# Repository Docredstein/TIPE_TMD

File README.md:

# TIPE_TMD
TIPE TMD 2022-2023
Ici se trouve le repo de notre TIPE ayant pour thème la ville, si vous êtes aussi en prépa libre à vous de vous inspirer, En cas de besoin vous pouvez envoyer un mail à
mateis. frambourt @laposte.net (sans les espaces) et je ferais de mon mieux pour vous aider.

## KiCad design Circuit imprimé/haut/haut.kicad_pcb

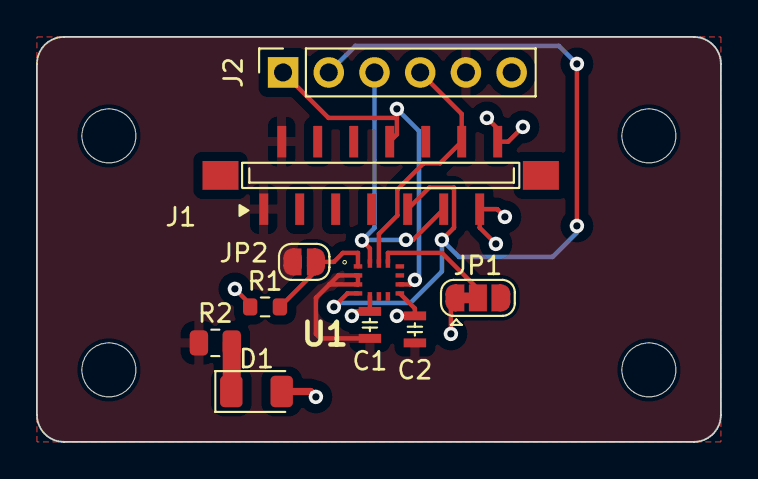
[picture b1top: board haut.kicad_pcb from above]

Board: 2 copper layers, 38.0 x 22.5 mm, 10 parts (0 on the bottom side), 9 nets.

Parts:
C1, C2: 100n; Cap 100nf 0805
D1: LED; LED_1206_3216Metric
J1: Conn_01x14_Shielded; FPC 2x7 p=1mm
J2: Conn_01x06_Male; PinSocket_1x06_P2.54mm_Vertical
JP1: SolderJumper_3_Bridged12; SolderJumper-3_P1.3mm_Bridged12_RoundedPad1.0x1.5mm
JP2: SolderJumper_2_Open; SolderJumper-2_P1.3mm_Open_RoundedPad1.0x1.5mm
R1: 10k; R_0603_1608Metric
R2: 30; R_0805_2012Metric
U1: LSM6DSRTR; LGA-14_2.5X3X0.86_

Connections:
+3V3: C1.1, C2.1, D1.2 (A), J1.13, J1.14, J2.6, JP1.1 (A), R1.1, U1.5 (VDD_IO), U1.8 (VDD)
GND: C1.2, C2.2, J1.1, J1.2, J2.5, JP2.2 (B), R2.1, U1.2 (SDX_), U1.3 (SCX)
INT1_Haut: J1.9, J2.2, U1.4 (INT1)
INT2_Haut: J1.8, J2.1, U1.9 (INT2)
unnamed: D1.1 (K), R2.2
unnamed: JP1.2 (C), U1.12 (CS)
unnamed: JP2.1 (A), R1.2, U1.1 (SDO/SA0)
SCL: J1.12, J2.4, U1.13 (SCL)
SDA: J1.11, J2.3, U1.14 (SDA)

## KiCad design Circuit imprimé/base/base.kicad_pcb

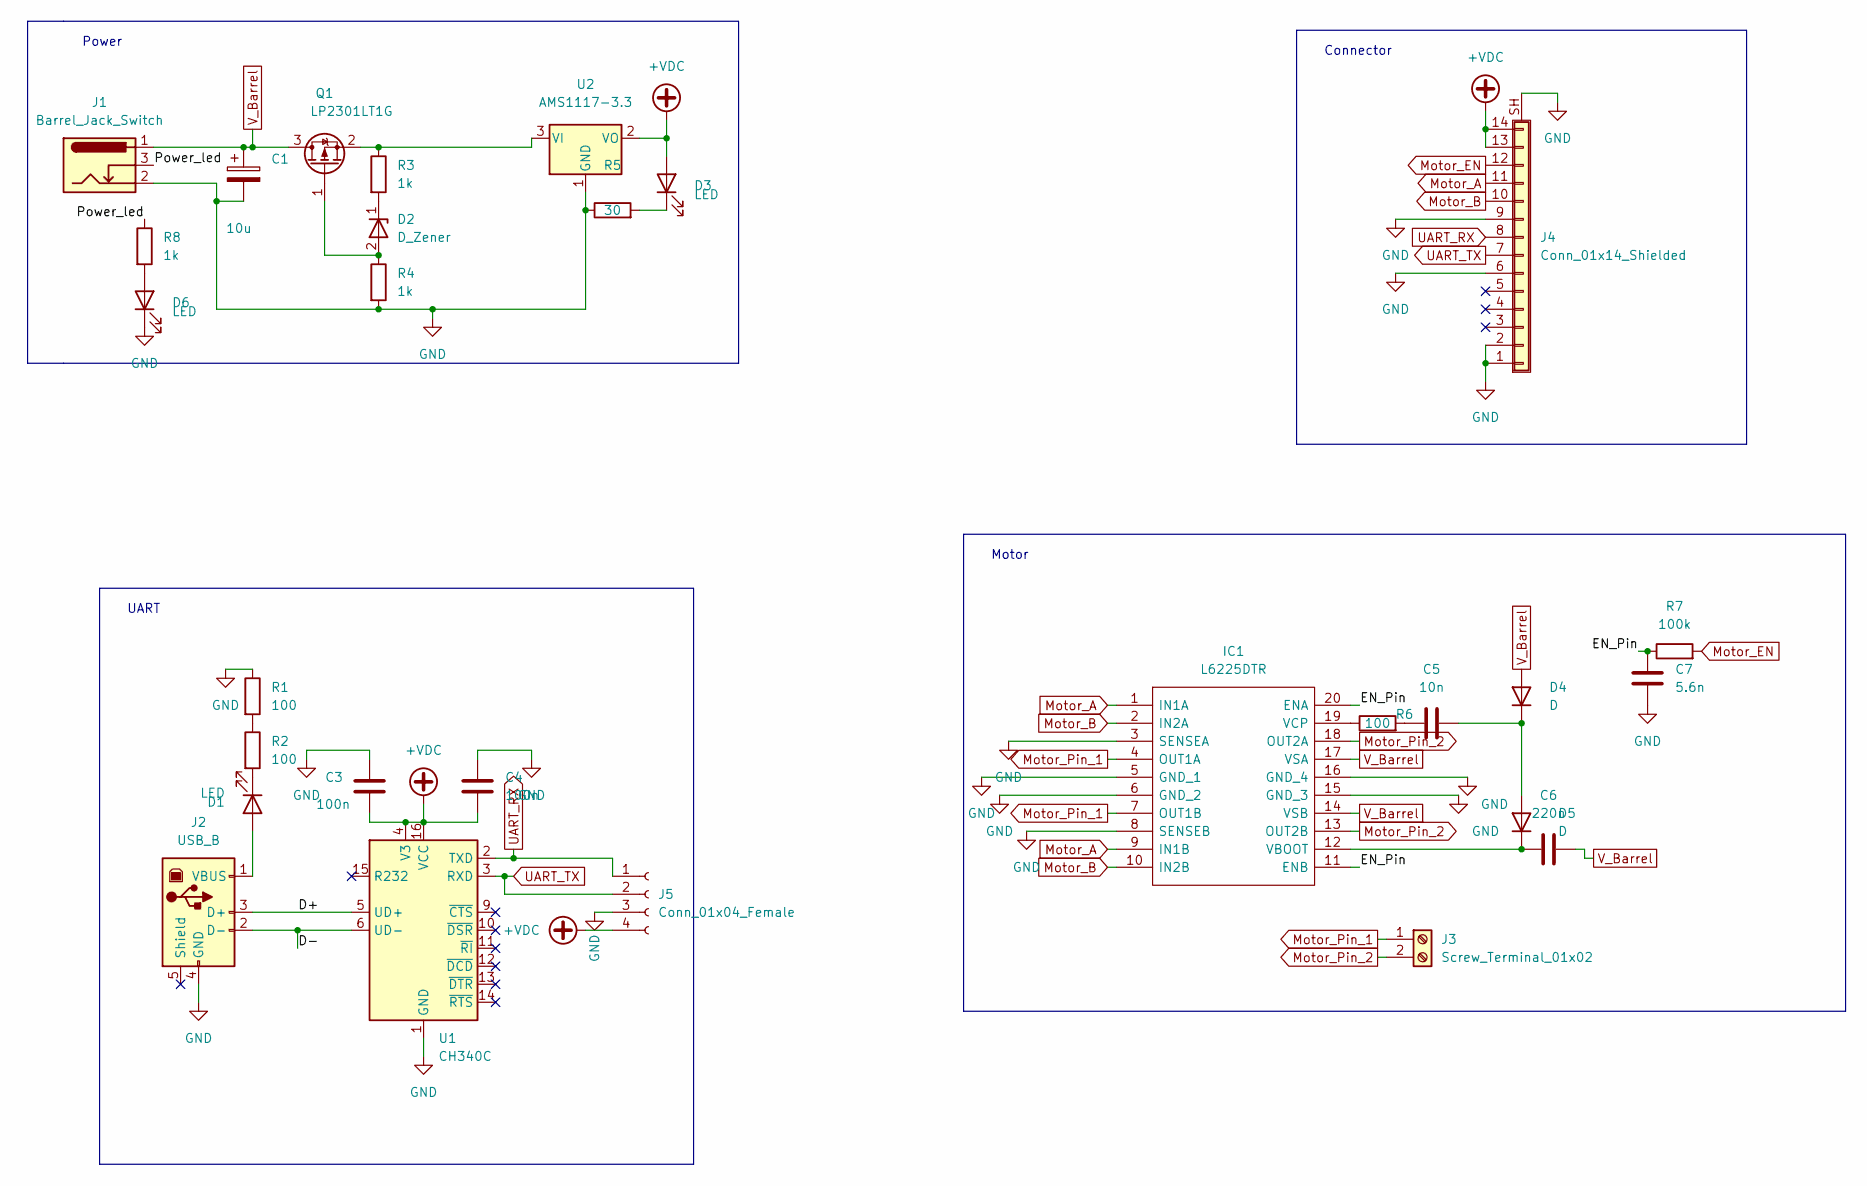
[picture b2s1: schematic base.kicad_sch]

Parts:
C1: 10u; CP_Elec_6.3x7.7
C3, C4: 100n; Cap 100nf 0805
C5: 10n; C_0805_2012Metric
C6: 220n; C_0805_2012Metric
C7: 5.6n; C_0603_1608Metric
D1, D3, D6: LED; LED_1206_3216Metric
D2: D_Zener; SOD223
D4, D5: D; D_SOD-323
IC1: L6225DTR; Mouser Part Number 511-L6225DTR
J1: Barrel_Jack_Switch; BarrelJack_GCT_DCJ200-10-A_Horizontal
J2: USB_B; USB_B_OST_USB-B1HSxx_Horizontal
J3: Screw_Terminal_01x02; TerminalBlock_Dinkle_DT-55-B01X-02_P10.00mm
J4: Conn_01x14_Shielded; FPC 2x7 p=1mm
J5: Conn_01x04_Female; PinSocket_1x04_P2.54mm_Horizontal
Q1: LP2301LT1G; SOT-23
R1, R2, R6: 100; R_0603_1608Metric
R3, R4, R8: 1k; R_0603_1608Metric
R5: 30; R_0805_2012Metric
R7: 100k; R_0603_1608Metric
U1: CH340C; SOIC-16_3.9x9.9mm_P1.27mm
U2: AMS1117-3.3; SOT-223-3_TabPin2

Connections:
+VDC: C3.2, C4.1, D3.2 (A), J4.13, J4.14, J5.4, U1.4 (V3), U1.16 (VCC), U2.2 (VO)
/D+: J2.3 (D+), U1.5 (UD+)
/D-: J2.2 (D-), U1.6 (UD-)
/EN_Pin: C7.2, IC1.11 (ENB), IC1.20 (ENA), R7.1
/Power_led: J1.3, R8.1
GND: C1.2, C3.1, C4.2, C7.1, D6.1 (K), IC1.3 (SENSEA), IC1.5 (GND_1), IC1.6 (GND_2), IC1.8 (SENSEB), IC1.15 (GND_3), IC1.16 (GND_4), J1.2, J2.4 (GND), J4.1, J4.2, J4.6, J4.9, J4.SH (Shield), J5.3, R1.1, R4.2, R5.1, U1.1 (GND), U2.1 (GND)
Motor_A: IC1.1 (IN1A), IC1.9 (IN1B), J4.11
Motor_B: IC1.2 (IN2A), IC1.10 (IN2B), J4.10
Motor_EN: J4.12, R7.2
Motor_Pin_1: IC1.4 (OUT1A), IC1.7 (OUT1B), J3.1
Motor_Pin_2: IC1.13 (OUT2B), IC1.18 (OUT2A), J3.2
unnamed: C5.1, R6.2
unnamed: C5.2, D4.1 (K), D5.2 (A)
unnamed: C6.1, D5.1 (K), IC1.12 (VBOOT)
unnamed: D1.1 (K), R2.2
unnamed: D1.2 (A), J2.1 (VBUS)
unnamed: D2.1 (K), R3.2
unnamed: D2.2 (A), Q1.1 (G), R4.1
unnamed: D3.1 (K), R5.2
unnamed: D6.2 (A), R8.2
unnamed: IC1.19 (VCP), R6.1
unnamed: Q1.2 (S), R3.1, U2.3 (VI)
unnamed: R1.2, R2.1
UART_RX: J4.8, J5.1, U1.2 (TXD)
UART_TX: J4.7, J5.2, U1.3 (RXD)
V_Barrel: C1.1, C6.2, D4.2 (A), IC1.14 (VSB), IC1.17 (VSA), J1.1, Q1.3 (D)

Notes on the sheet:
Power
Motor
UART
Connector

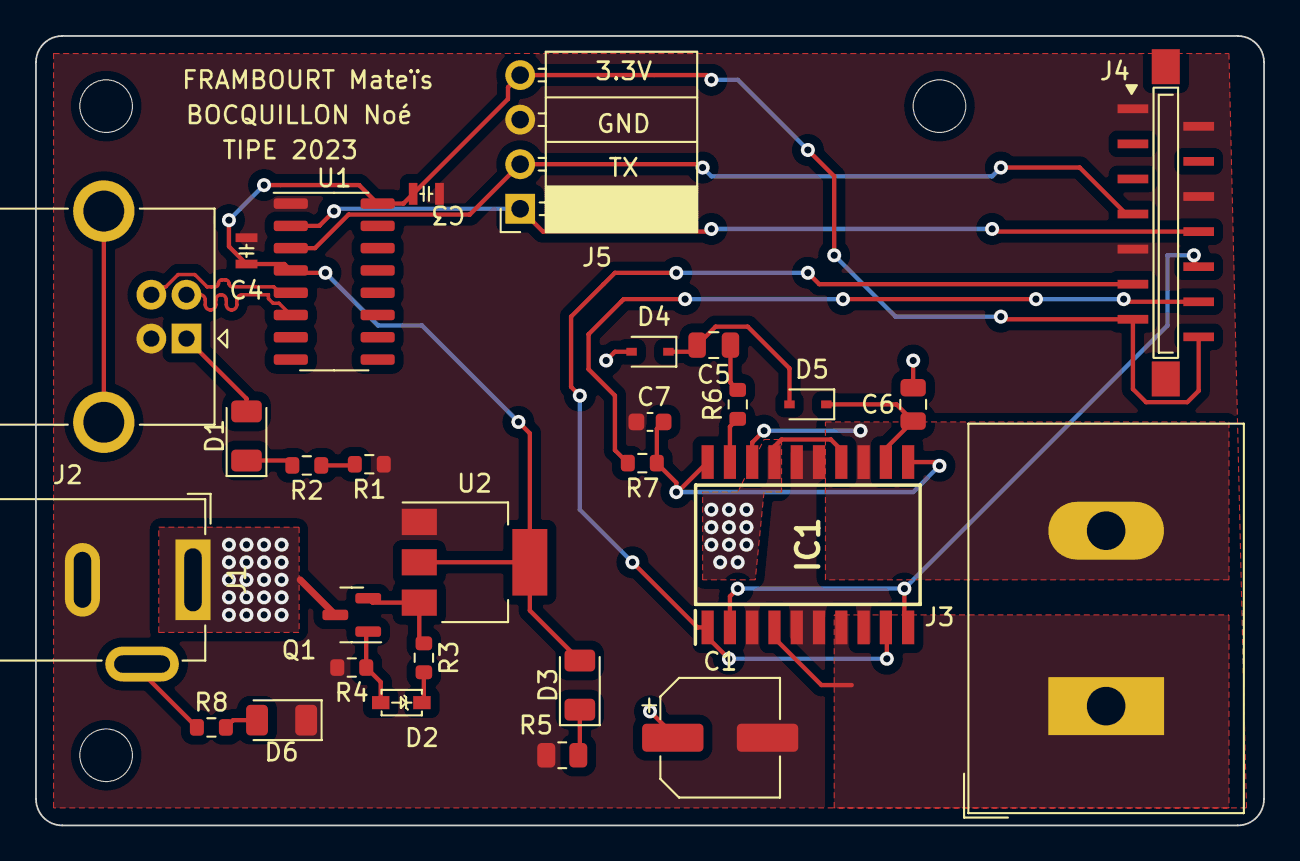
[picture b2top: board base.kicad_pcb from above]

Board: 2 copper layers, 70.0 x 45.0 mm, 29 parts (0 on the bottom side), 26 nets.

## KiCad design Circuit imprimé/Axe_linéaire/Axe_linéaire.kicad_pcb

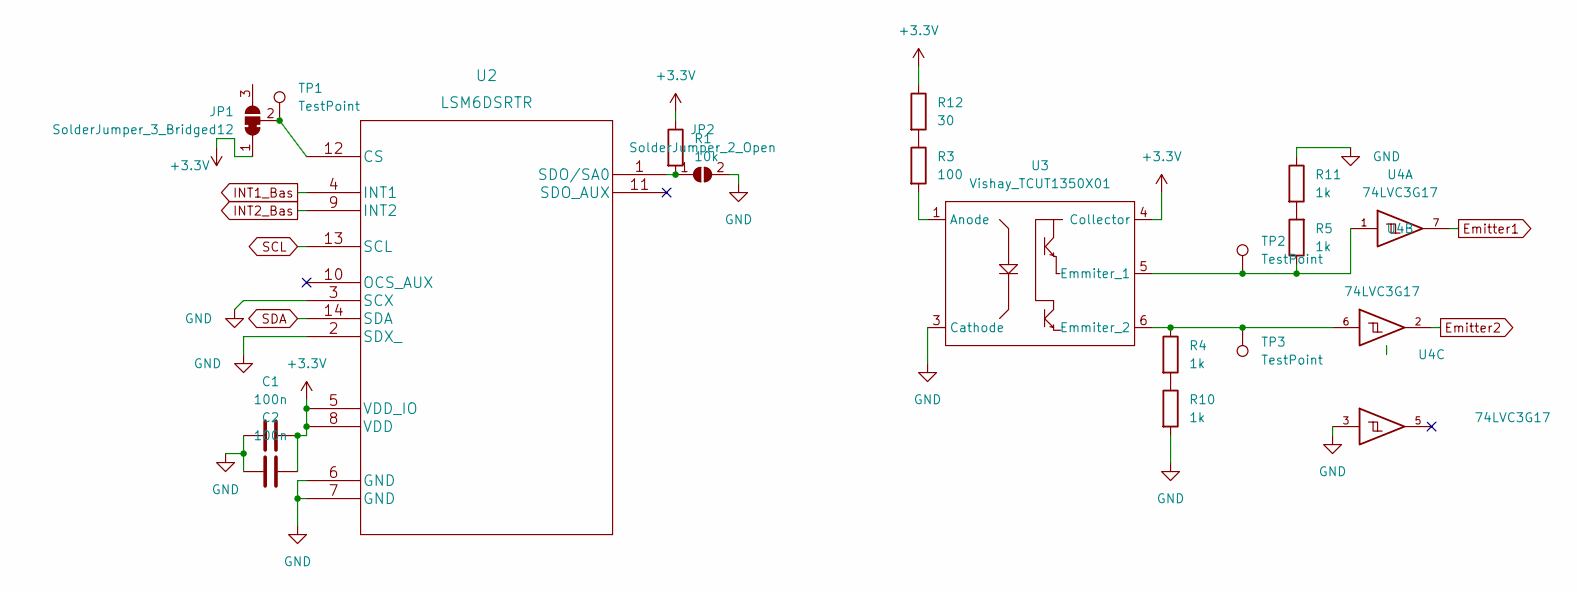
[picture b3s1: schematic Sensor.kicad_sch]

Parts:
C1, C2: 100n; Cap 100nf 0805
JP1: SolderJumper_3_Bridged12; SolderJumper-3_P1.3mm_Bridged12_RoundedPad1.0x1.5mm
JP2: SolderJumper_2_Open; SolderJumper-2_P1.3mm_Open_RoundedPad1.0x1.5mm
R1: 10k; R_0603_1608Metric
R3: 100; R_0603_1608Metric
R4, R5, R10, R11: 1k; R_0603_1608Metric
R12: 30; R_0805_2012Metric
TP1, TP2, TP3: TestPoint; TestPoint_Pad_D2.0mm
U2: LSM6DSRTR; LGA-14_2.5X3X0.86_
U3: Vishay_TCUT1350X01; Vishay TCUT1350X01
U4: 74LVC3G17; VSSOP-8_2.3x2mm_P0.5mm

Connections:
+3.3V: C1.1, C2.1, JP1.1 (A), R1.1, R12.1, U2.5 (VDD_IO), U2.8 (VDD), U3.4 (Collector), U4.8 (+3.3V); also elsewhere on the board
Emitter1: U4.7; also elsewhere on the board
Emitter2: U4.2; also elsewhere on the board
GND: C1.2, C2.2, JP2.2 (B), R10.2, R11.1, U2.2 (SDX_), U2.3 (SCX), U2.6 (GND), U2.7 (GND), U3.3 (Cathode), U4.3, U4.4 (GND); also elsewhere on the board
INT1_Bas: U2.4 (INT1); also elsewhere on the board
INT2_Bas: U2.9 (INT2); also elsewhere on the board
unnamed: JP1.2 (C), TP1.1, U2.12 (CS)
unnamed: JP2.1 (A), R1.2, U2.1 (SDO/SA0)
unnamed: R3.2, U3.1 (Anode)
unnamed: R4.1, TP3.1, U3.6 (Emmiter_2), U4.6
unnamed: R5.1, TP2.1, U3.5 (Emmiter_1), U4.1
unnamed: R4.2, R10.1
unnamed: R5.2, R11.2
unnamed: R3.1, R12.2
SCL: U2.13 (SCL); also elsewhere on the board
SDA: U2.14 (SDA); also elsewhere on the board

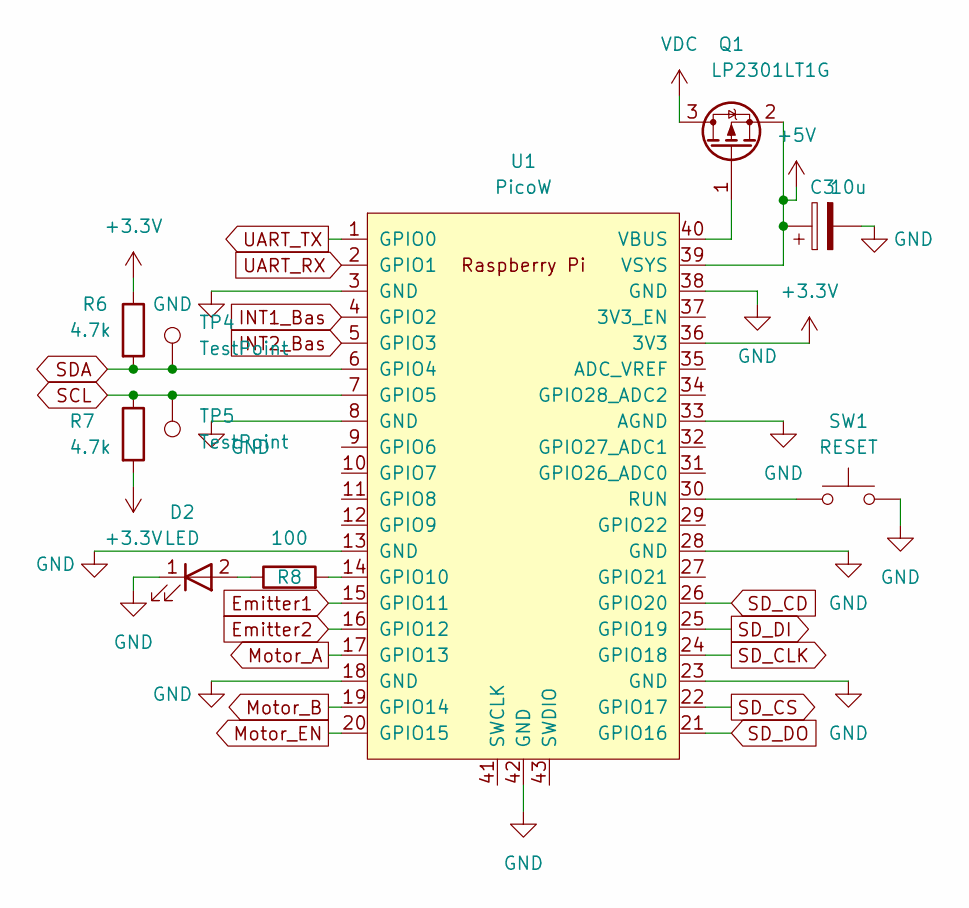
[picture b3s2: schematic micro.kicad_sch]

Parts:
C3: 10u; CP_Elec_6.3x7.7
D2: LED; UV_LED
Q1: LP2301LT1G; SOT-23
R6, R7: 4.7k; R_0603_1608Metric
R8: 100; R_0603_1608Metric
SW1: RESET; Tactile Button
TP4, TP5: TestPoint; TestPoint_Pad_D2.0mm
U1: PicoW; RPi_PicoW_SMD_TH

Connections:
+3.3V: R6.1, R7.2, U1.36 (3V3); also elsewhere on the board
+5V: C3.1, Q1.2 (S), U1.39 (VSYS)
Emitter1: U1.15 (GPIO11); also elsewhere on the board
Emitter2: U1.16 (GPIO12); also elsewhere on the board
GND: C3.2, D2.1 (K), SW1.3 (B), SW1.4 (B), U1.3 (GND), U1.8 (GND), U1.13 (GND), U1.18 (GND), U1.23 (GND), U1.28 (GND), U1.33 (AGND), U1.38 (GND), U1.42 (GND); also elsewhere on the board
INT1_Bas: U1.4 (GPIO2); also elsewhere on the board
INT1_Haut: U1.9 (GPIO6); also elsewhere on the board
INT2_Bas: U1.5 (GPIO3); also elsewhere on the board
INT2_Haut: U1.10 (GPIO7); also elsewhere on the board
Motor_A: U1.17 (GPIO13); also elsewhere on the board
Motor_B: U1.19 (GPIO14); also elsewhere on the board
Motor_EN: U1.20 (GPIO15); also elsewhere on the board
unnamed: D2.2 (A), R8.1
unnamed: Q1.1 (G), U1.40 (VBUS)
unnamed: R8.2, U1.14 (GPIO10)
unnamed: SW1.1 (A), SW1.2 (A), U1.30 (RUN)
SCL: R7.1, TP5.1, U1.7 (GPIO5); also elsewhere on the board
SDA: R6.2, TP4.1, U1.6 (GPIO4); also elsewhere on the board
SD_CD: U1.26 (GPIO20); also elsewhere on the board
SD_CLK: U1.24 (GPIO18); also elsewhere on the board
SD_CS: U1.22 (GPIO17); also elsewhere on the board
SD_DI: U1.25 (GPIO19); also elsewhere on the board
SD_DO: U1.21 (GPIO16); also elsewhere on the board
UART_RX: U1.2 (GPIO1); also elsewhere on the board
UART_TX: U1.1 (GPIO0); also elsewhere on the board
VDC: Q1.3 (D); also elsewhere on the board

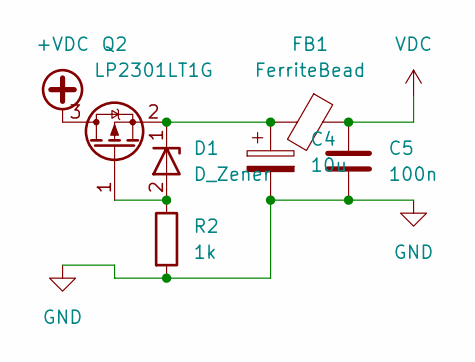
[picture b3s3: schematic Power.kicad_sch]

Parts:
C4: 10u; CP_Elec_6.3x7.7
C5: 100n; Cap 100nf 0805
D1: D_Zener; SOD223
FB1: FerriteBead; ferrite Bead
Q2: LP2301LT1G; SOT-23
R2: 1k; R_0603_1608Metric

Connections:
+VDC: Q2.3 (D); also elsewhere on the board
GND: C4.2, C5.2, R2.2; also elsewhere on the board
unnamed: C4.1, D1.1 (K), FB1.2, Q2.2 (S)
unnamed: D1.2 (A), Q2.1 (G), R2.1
VDC: C5.1, FB1.1; also elsewhere on the board

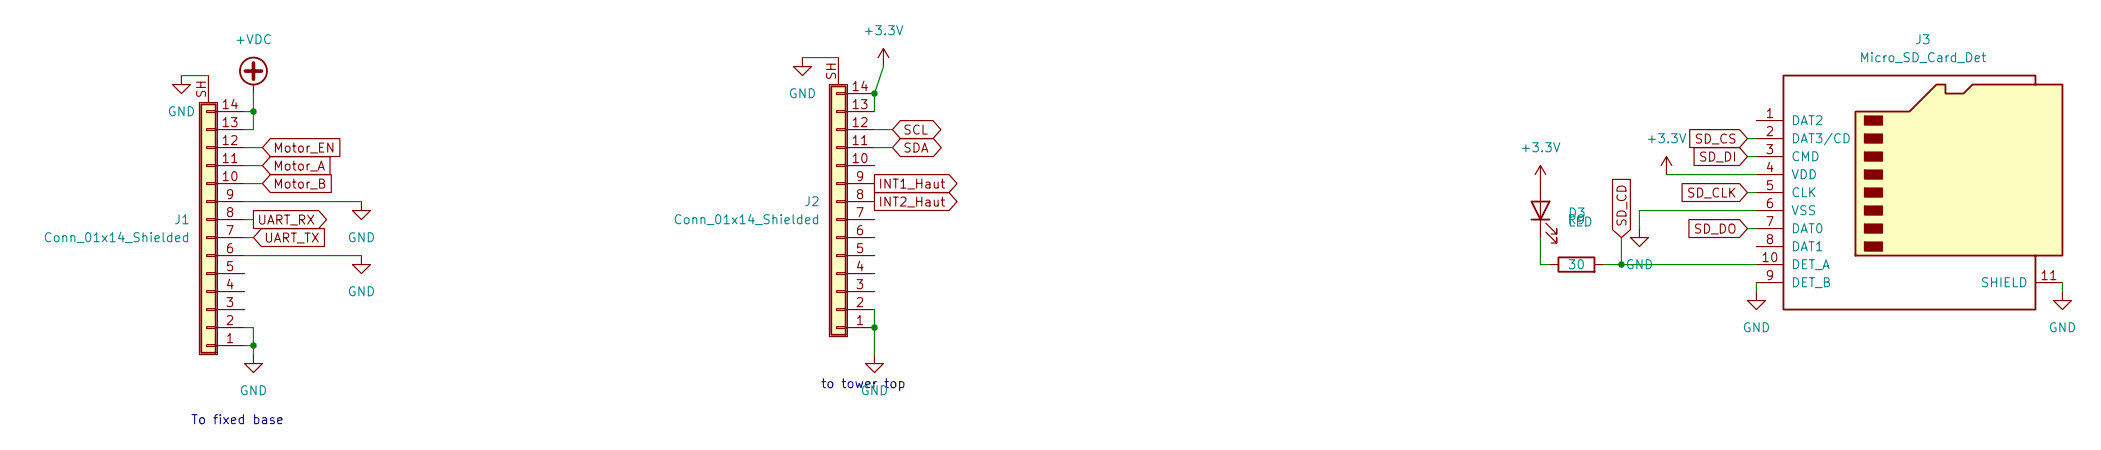
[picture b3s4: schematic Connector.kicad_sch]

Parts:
D3: LED; LED_1206_3216Metric
J1, J2: Conn_01x14_Shielded; FPC 2x7 p=1mm
J3: Micro_SD_Card_Det; microSD_HC_Hirose_DM3AT-SF-PEJM5
R9: 30; R_0805_2012Metric

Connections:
+3.3V: D3.2 (A), J2.13, J2.14, J3.4 (VDD); also elsewhere on the board
+VDC: J1.13, J1.14; also elsewhere on the board
GND: J1.1, J1.2, J1.6, J1.9, J1.SH (Shield), J2.1, J2.2, J2.SH (Shield), J3.6 (VSS), J3.9 (DET_B), J3.11 (SHIELD); also elsewhere on the board
INT1_Haut: J2.9; also elsewhere on the board
INT2_Haut: J2.8; also elsewhere on the board
Motor_A: J1.11; also elsewhere on the board
Motor_B: J1.10; also elsewhere on the board
Motor_EN: J1.12; also elsewhere on the board
unnamed: D3.1 (K), R9.1
SCL: J2.12; also elsewhere on the board
SDA: J2.11; also elsewhere on the board
SD_CD: J3.10 (DET_A), R9.2; also elsewhere on the board
SD_CLK: J3.5 (CLK); also elsewhere on the board
SD_CS: J3.2 (DAT3/CD); also elsewhere on the board
SD_DI: J3.3 (CMD); also elsewhere on the board
SD_DO: J3.7 (DAT0); also elsewhere on the board
UART_RX: J1.8; also elsewhere on the board
UART_TX: J1.7; also elsewhere on the board

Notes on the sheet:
To fixed base
to tower top

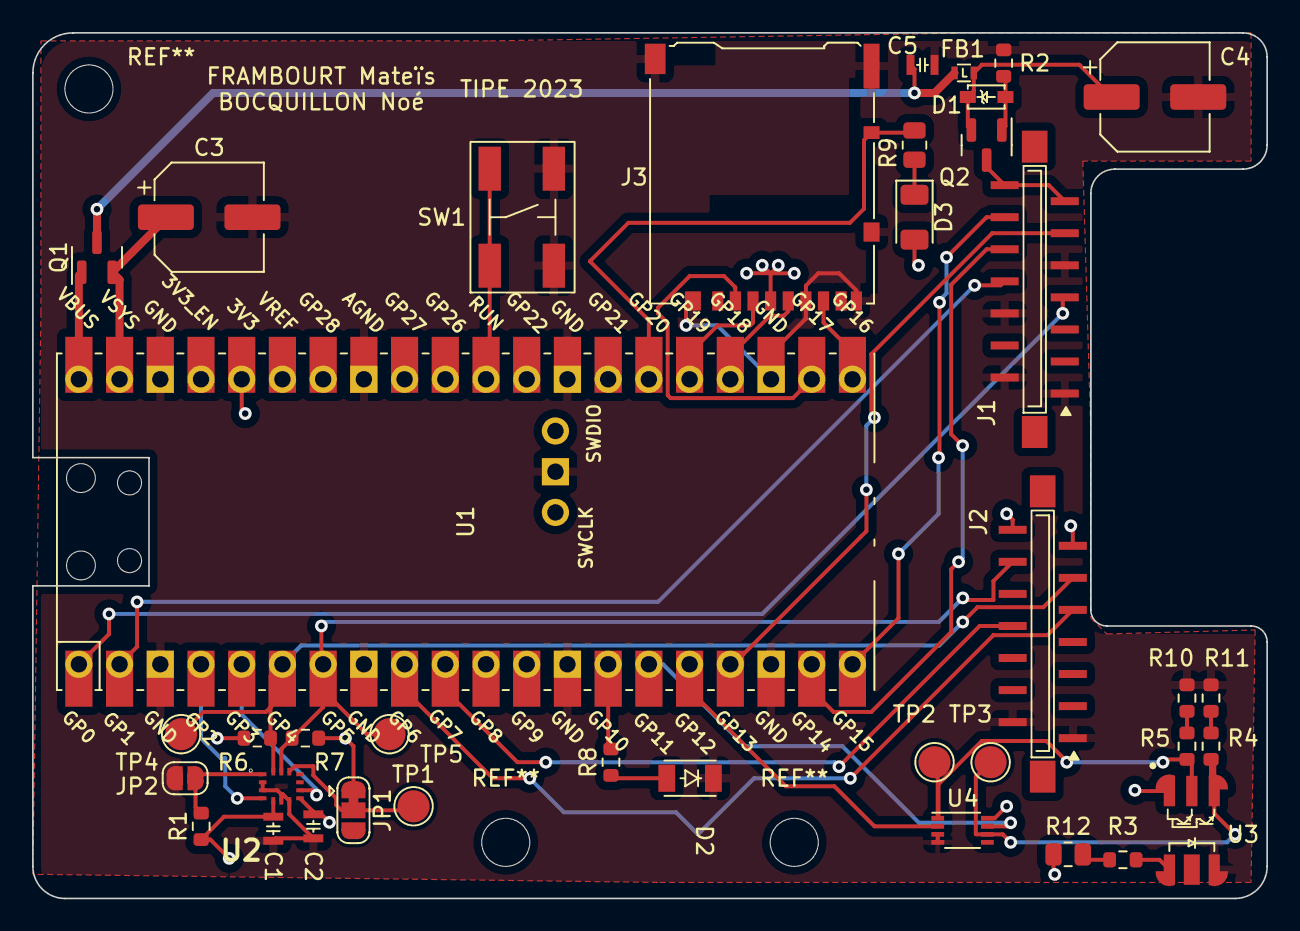
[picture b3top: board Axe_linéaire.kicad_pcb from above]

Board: 2 copper layers, 77.0 x 54.0 mm, 38 parts (0 on the bottom side), 38 nets.

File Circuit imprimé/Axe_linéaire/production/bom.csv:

Designator,Footprint,Quantity,Value,LCSC Part #
"C1, C2, C5",Cap 100nf 0805,3,100n,
"C3, C4",CP_Elec_6.3x7.7,2,10u,
D1,SOD223,1,D_Zener,
D2,UV_LED,1,LED,
D3,1206,1,LED,
FB1,ferrite Bead,1,FerriteBead,
"J1, J2",FPC 2x7 p=1mm,2,Conn_01x14_Shielded,
J3,microSD_HC_Hirose_DM3AT-SF-PEJM5,1,Micro_SD_Card_Det,
JP1,SolderJumper-3_P1.3mm_Bridged12_RoundedPad1.0x1.5mm,1,SolderJumper_3_Bridged12,
JP2,SolderJumper-2_P1.3mm_Open_RoundedPad1.0x1.5mm,1,SolderJumper_2_Open,
"Q1, Q2",SOT-23,2,LP2301LT1G,
R1,0603,1,10k,
R10,0603,1,1k,
R11,0603,1,1k,
R12,0805,1,30,
R2,0603,1,1k,
R3,0603,1,100,
R4,0603,1,1k,
R5,0603,1,1k,
R6,0603,1,4.7k,
R7,0603,1,4.7k,
R8,0603,1,100,
R9,0805,1,30,
SW1,Tactile Button,1,RESET,
"TP1, TP2, TP3, TP4, TP5",TestPoint_Pad_D2.0mm,5,TestPoint,
U1,RPi_PicoW_SMD_TH,1,PicoW,
U2,LGA-14_2.5X3X0.86_,1,LSM6DSRTR,
U3,Vishay TCUT1350X01,1,Vishay_TCUT1350X01,
U4,VSSOP-8_2.3x2mm_P0.5mm,1,74LVC3G17,

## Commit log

2022-10-06 initial
2023-01-23 janvier
2023-02-04 Début de la phase de prototipage du PCB (tout Début)
2023-02-05 Ajout de button et pico w
2023-02-13 Ajout du transitor d'OR de l'alim
2023-02-13 choix et création des Connector_FFC
2023-02-13 Ajout des protections sur l'alimentation
2023-02-14 Ajout de l'IMU + modèle du photointerrupteur
2023-02-14 ajout du circuit de position + carte SD
2023-02-14 Création du circuit imprimé
2023-02-14 circuit V1
2023-02-16 1er circuit fini, schéma de la base fini
2023-02-16 fin du circuit de base
2023-02-17 tout mes CI sont pret
2023-02-21 circuit imprimé commandé
2023-02-21 début fw
2023-02-23 fw start
2023-02-23 cleannup
2023-02-24 added gitignore
2023-02-25 Début de la librairie de controle moteur
2023-02-25 updated gitignore
2023-02-26 Finished motor control
2023-02-27 prototype PID
2023-02-27 prototype
2023-02-28 PID complete
2023-03-01 added SD submodule + resolved error in error calculation
2023-03-01 added logging
2023-03-01 fixed abs value for PID
2023-03-01 début acc
2023-03-02 ajout des mesures
2023-03-02 calcul force rappel
2023-03-05 assemblage et prise en photo du CI
2023-03-06 created i2c access
2023-03-06 Tested Sensor ==> Working :D
2023-03-07 added sensor readout
2023-03-08 Sensor readout optimization
2023-03-09 début software
2023-03-09 Software
2023-03-11 fonction de base faite
2023-03-12 rednu
2023-03-16 Modif software
2023-03-20 Firmware fini ?
2023-03-20 image
2023-03-24 test traitement des données
2023-03-30 Mesure, pb spin
2023-04-06 Mesure multiple
2023-04-28 Automatisation diagramme de Bode
2023-05-05 Traitement de toute les mesures à l'heure actuelle
2023-05-05 traité tout
2023-05-05 touche finale(pour l'instant)
2023-05-15 Mesure très faible amplitude
2023-05-16 mesure tres faible ampitude finie
2023-05-16 mesures avec masse de 73g
2023-05-21 Tri photo
2023-05-22 TIPE quasi préparé
2023-05-30 schéma
2023-06-02 Passage ENS
2023-06-04 bonne freq
